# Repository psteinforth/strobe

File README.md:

# strobe
ATtiny microcontroller project to control a cheap stroboscope or similar device. 

### Introduction
This piece of software was designed to enable a cheap LED stroboscope by people on a danceflor. The strobe flashes as long as it is powered. The idea was to enable the strobe for a fixed time period as soon as a dancer presses a red push-button. To avoid nearly continuous flashing due to drunken people :dancers: the strobe can not be reenabled before a configurable time period passed.

### Features
- Based on Atmel ATtiny 44A-PU microcontroller.
- Interrupt-driven recognition of push-button presses.
- Strobe activity time period is configurable by a potentiometer.
- Time period between two strobe activites is potentiometer controllable.
- Status LED for "push button active/ strobe can be enabled" and "strobe active".
- Automatic reset in case of a microcontroller hang-up by watchdog timer within 0.125 seconds.

### Details
- Some options are configurable by **preprocessor defines**. Default values will be used if they are not given. Meaning of preprocessor defines can be found in source code comments.
- Program sequence is controlled by a **Finite State Machine**
    - Legend (0 = no/not required, 1 = yes/required, -1 = unspecified/don't care)
        - buzzer_enabled (output): push-button is active and can enable the strobe
        - relais_enabled (output): relais is active and powers the strobe
        - buzzer_pressed (input): push-button was pressed
        - timer_counting (input): timer is active (strobe active or buzzer locked and time is not over)
        - next_state: new state that will be selected if all inputs met the current state
    - State transition matrix:

State | Name | buzzer_enabled | relais_enabled | buzzer_pressed | timer_counting | next_state
------|------|----------------|----------------|----------------|----------------|------------
S_0 | WAIT_FOR_KEYPRESS | 1 | 0 | 1 | -1 | BLINKING
S_1 | BLINKING | 0 | 1 | -1 | 0 | BUZZER_LOCKED
S_2 | BUZZER_LOCKED | 0 | 0 | -1 | 0 | WAIT_FOR_KEYPRESS

State transition diagram (arrows are labeled with inputs that are required for state change):

- All **time periods** are counted  by 16-bit Timer/Counter 1
- **Push-putton** presses are detected by external interrupt INT0
- **Potentiometers** are sampled by analog/digital converter (ADC)
    - Sampling is conducted only once after each power on/reset. So the adjustment of potentiometers is not detected until next microcontroller reset/restart.
    - This program does not use the low noise mode while sampling potentiometer values. However for better sampling results an averaged value of several (configurable by preprocessor define) samplings is calculated. In addition for every potentiometer an additional sampling is done first to stabilize the ADC, the value of this conversion is thrown.
- The circuit should be **power**ed with 5 V (DC). In other cases maybe other and/or additional components are required. It's recommended to enable the brown-out detector to reset the microcontroller if the current falls below a certain level (maybe 4.3 V).

### Microcontroller connections
Legend:
- *Italic* pins are required for In-System-Programming (ISP) via SPI. Pins printed grey additonally are only required for ISP.
- AREF is not connected but maybe will be used for more precise potentiometer values later. 

### Circuit Diagram

### Conductor board example

### Known issues
- __External Interrupt enabled unintentional.__
Under some circumstances (noisy environments) the external interrupt is triggered by electrical interferences. This maybe could be solved by implementing a debouncing algorithm to detect button presses and/or additonal hardware like external pull up resistors, a low pass filter or capacitors at the right place.

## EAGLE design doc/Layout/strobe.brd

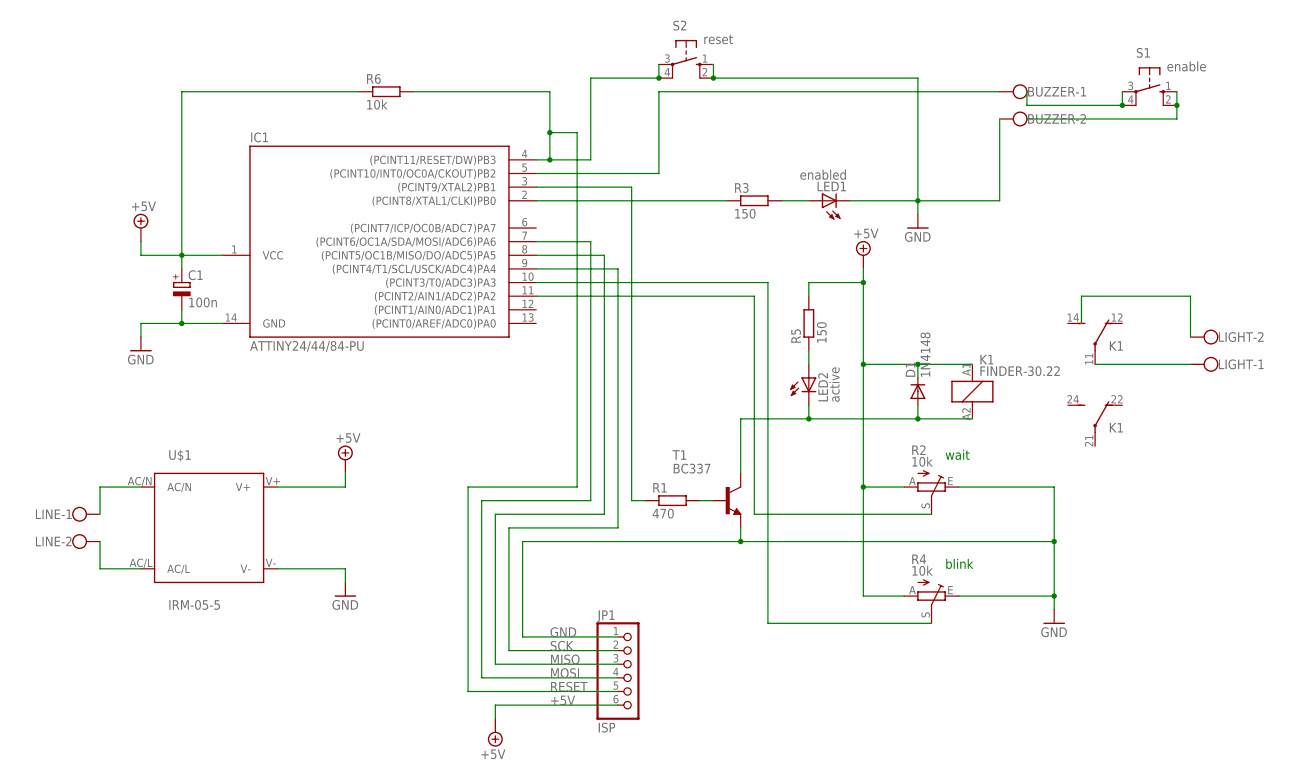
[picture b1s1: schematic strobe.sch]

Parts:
BUZZER: W237-102
C1: 100n; E2,5-6E
D1: 1N4148; DO35-7
IC1: ATTINY24/44/84-PU; DIL14
JP1: ISP; 1X06
K1: FINDER-30.22
LED1: enabled; LED3MM
LED2: active; LED3MM
LIGHT: W237-102
LINE: W237-102
R1: 470; 0207/10
R2, R4: 10k; CA6V
R3, R5: 150; 0207/10
R6: 10k; 0207/10
S1: enable; B3F-10XX
S2: reset; B3F-10XX
T1: BC337; TO92
U$1: IRM-05-5; IRM_05/10

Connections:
+5V: C1.+, D1.C, IC1.1 (VCC), JP1.6, K1.A1 (1), R2.A, R4.A, R5.2, R6.1
GND: BUZZER.2, C1.-, IC1.14 (GND), JP1.1, LED1.K (C), R2.E, R4.E, S2.1 (S), S2.2 (S1), T1.1 (E), U$1.V-
MISO: IC1.8 ((PCINT5/OC1B/MISO/DO/ADC5)PA5), JP1.3
MOSI: IC1.7 ((PCINT6/OC1A/SDA/MOSI/ADC6)PA6), JP1.4
unnamed: LINE.1, U$1.AC/N
unnamed: IC1.3 ((PCINT9/XTAL2)PB1), R1.1
unnamed: R1.2, T1.2 (B)
unnamed: IC1.11 ((PCINT2/AIN1/ADC2)PA2), R2.S
unnamed: IC1.10 ((PCINT3/T0/ADC3)PA3), R4.S
unnamed: D1.A, K1.A2 (2), LED2.K (C), T1.3 (C)
unnamed: LED1.A, R3.2
unnamed: IC1.2 ((PCINT8/XTAL1/CLKI)PB0), R3.1
unnamed: BUZZER.1, IC1.5 ((PCINT10/INT0/OC0A/CKOUT)PB2)
unnamed: K1.11, LIGHT.1
unnamed: LED2.A, R5.1
unnamed: S1.1 (S), S1.2 (S1)
unnamed: S1.3, S1.4 (P1)
RESET: IC1.4 ((PCINT11/RESET/DW)PB3), JP1.5, R6.2, S2.3, S2.4 (P1)
SCK: IC1.9 ((PCINT4/T1/SCL/USCK/ADC4)PA4), JP1.2

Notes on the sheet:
blink
wait

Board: 2 copper layers, 20 parts (0 on the bottom side), 19 nets, no tracks yet.

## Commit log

2016-12-22 add gitignore
2016-12-22 Add project template
2016-12-23 add some stuff
2016-12-25 working without any features and without push button debouncing
2016-12-25 fixed push button debouncing
2016-12-27 add stuff for potentiometer input
2016-12-27 blinking and blocking time is adjustable
2016-12-28 turn ADC off after conversion
2016-12-28 new feature: buzzer locked interval configurable
2016-12-29 add state transition diagram
2016-12-29 change README
2016-12-29 improve doc
2016-12-29 add microcontroller pinout scheme
2016-12-31 set new define values
2017-01-07 add circuit diagram
2017-01-08 update circuit diagram
2017-01-08 add some pictures
2017-01-08 update doc
